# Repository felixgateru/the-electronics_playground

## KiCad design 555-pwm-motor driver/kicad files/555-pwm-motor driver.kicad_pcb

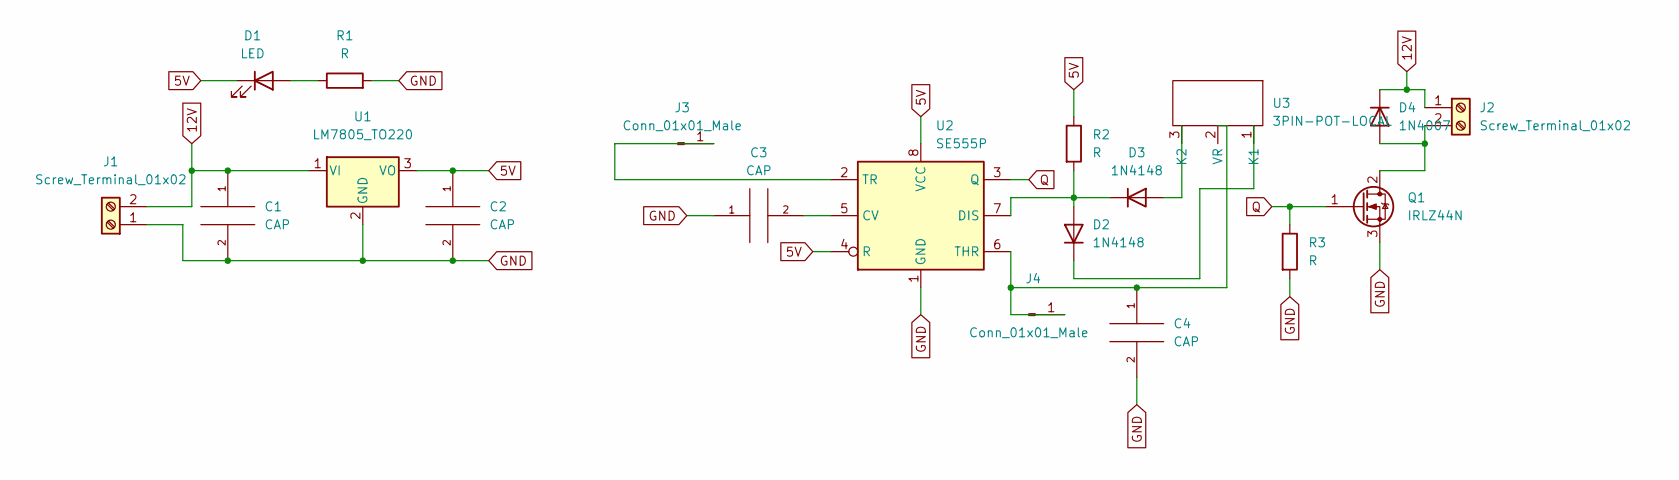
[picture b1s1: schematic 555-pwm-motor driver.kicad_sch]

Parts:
C1: CAP; CP_Radial_D5.0mm_P2.50mm
C2, C3, C4: CAP; CP_Radial_D4.0mm_P2.00mm
D1: LED; LED_D5.0mm
D2, D3: 1N4148; D_DO-35_SOD27_P7.62mm_Horizontal
D4: 1N4007; D_DO-41_SOD81_P10.16mm_Horizontal
J1, J2: Screw_Terminal_01x02; TerminalBlock_Phoenix_MKDS-1,5-2-5.08_1x02_P5.08mm_Horizont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
J3, J4: Conn_01x01_Male; PinHeader_1x01_P1.00mm_Vertical
Q1: IRLZ44N; TO-220-3_Vertical
R1, R2, R3: R; R_Axial_DIN0207_L6.3mm_D2.5mm_P7.62mm_Horizontal
U1: LM7805_TO220; TO-220-3_Vertical
U2: SE555P; DIP-8_W7.62mm
U3: 3PIN-POT-LOCAL; 3PIN-POT-LOCAL-5.08

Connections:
5V: C2.1, D1.1 (K), R2.1, U1.3 (VO), U2.4 (R), U2.8 (VCC)
12V: C1.1, D4.1 (K), J1.2, J2.1, U1.1 (VI)
GND: C1.2, C2.2, C3.1, C4.2, J1.1, Q1.3 (S), R1.2, R3.2, U1.2 (GND), U2.1 (GND)
unnamed: C3.2, U2.5 (CV)
unnamed: C4.1, J4.1, U2.6 (THR), U3.2 (VR)
unnamed: D1.2 (A), R1.1
unnamed: D2.1 (K), U3.1 (K1)
unnamed: D2.2 (A), D3.1 (K), R2.2, U2.7 (DIS)
unnamed: D3.2 (A), U3.3 (K2)
unnamed: D4.2 (A), J2.2, Q1.2 (D)
unnamed: J3.1, U2.2 (TR)
Q: Q1.1 (G), R3.1, U2.3 (Q)

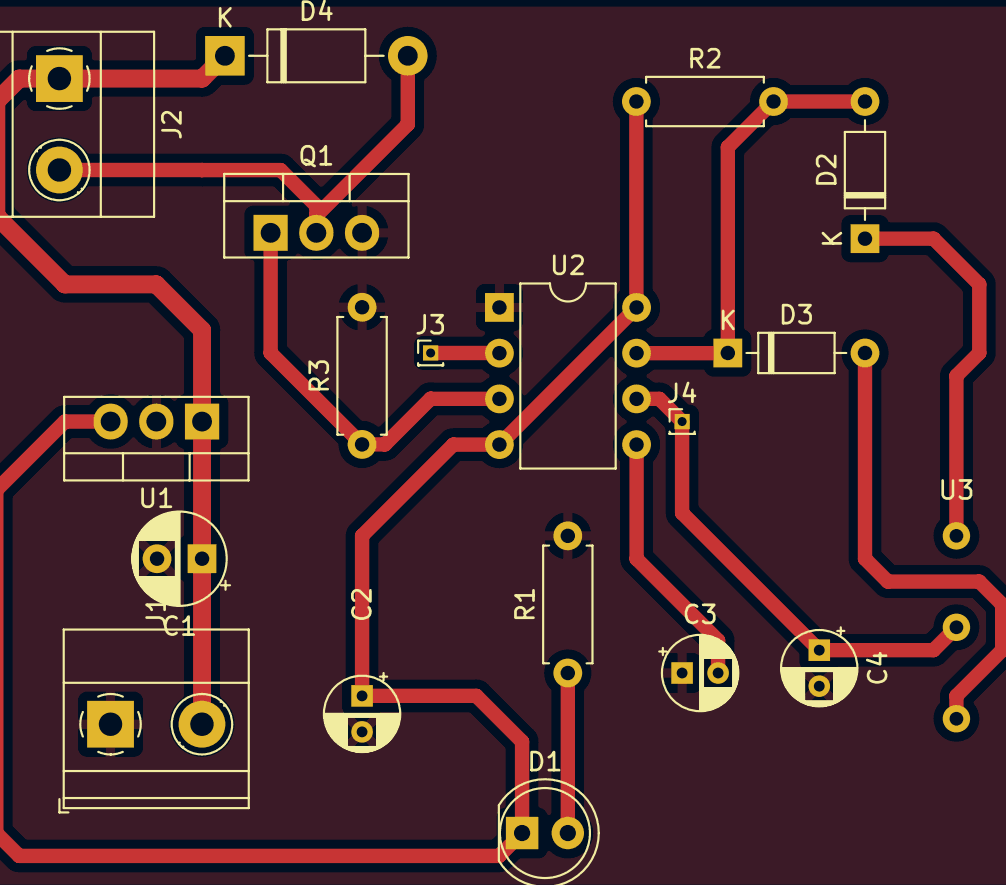
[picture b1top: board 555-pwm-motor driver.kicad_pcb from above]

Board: 2 copper layers, 19 parts (0 on the bottom side), 12 nets.

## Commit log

2022-09-10 Adding simulation files for project
2022-09-11 Adding pcb files
2022-09-11 Adding routing
2022-09-14 Adding pcb files-closes #1
2022-09-15 Cleaning up pcb
2022-09-15 Adding fab files
2022-09-15 Adding layout file
2022-10-16 Adding new project
2022-11-12 Add new test
